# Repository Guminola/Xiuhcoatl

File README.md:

# Xiuhcoatl
Repositories of the Xiuhcoatl mission

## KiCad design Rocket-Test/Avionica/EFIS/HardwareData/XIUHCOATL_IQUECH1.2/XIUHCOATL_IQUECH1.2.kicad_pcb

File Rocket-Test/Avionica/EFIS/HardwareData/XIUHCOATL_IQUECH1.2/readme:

/*
  VERSION: XIUHCOATL_IQUECH 1.2

  PCB FILES
  KICAD:
  ".sch"=Esquema
  ".net"=Lista de Redes
  ".kicad_pcb"=PCB
  
  SPACE>COHETERIA>DIVEC>Jorge Guerrero
*/

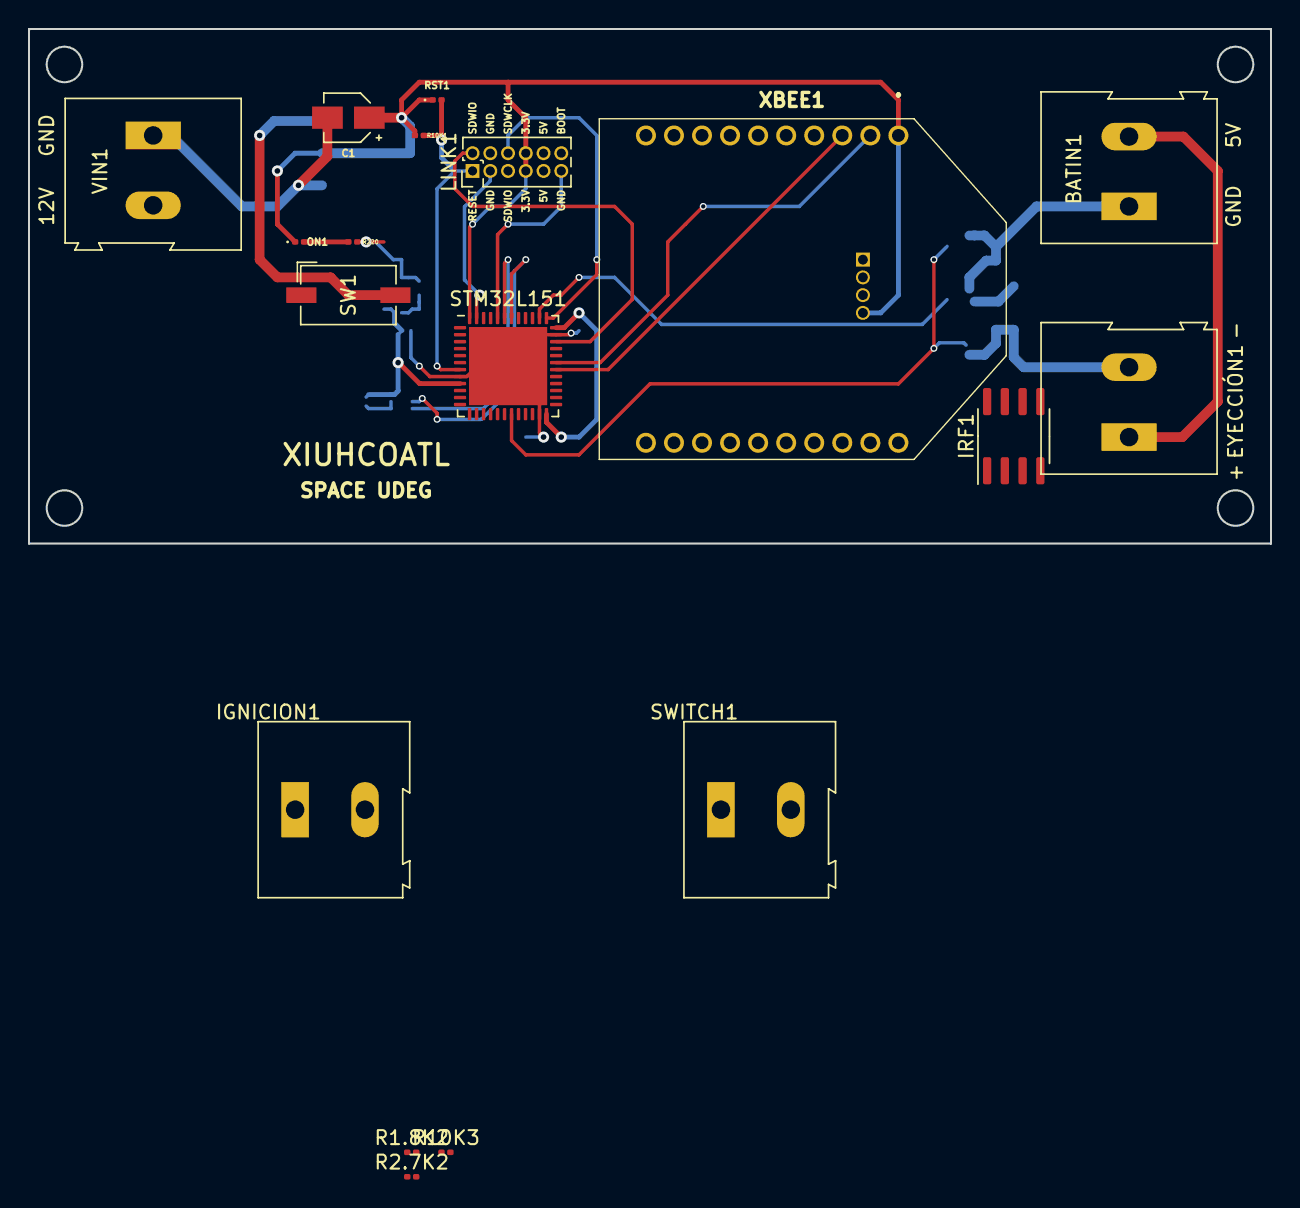
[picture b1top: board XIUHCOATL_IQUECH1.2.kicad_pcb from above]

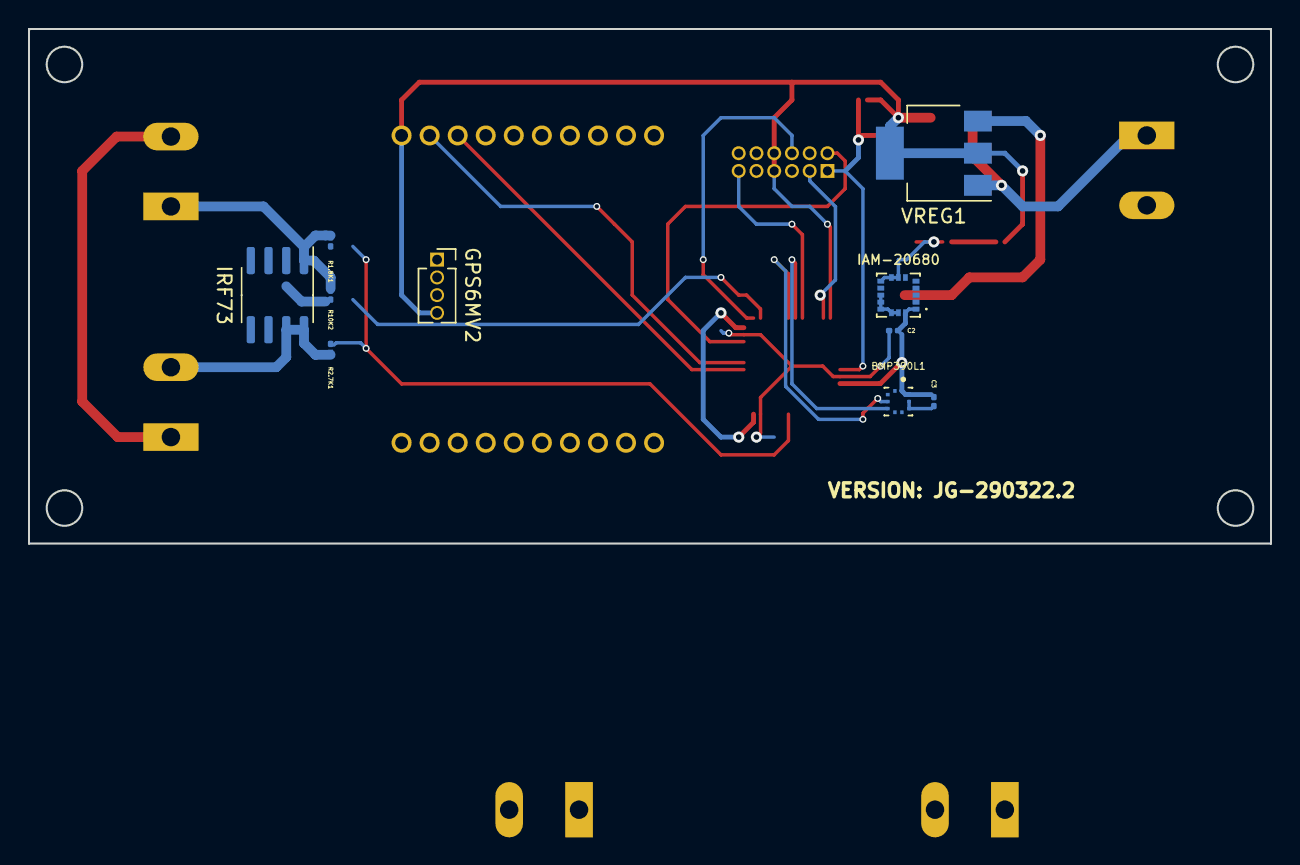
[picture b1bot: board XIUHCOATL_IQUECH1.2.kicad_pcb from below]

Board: 2 copper layers, 88.9 x 36.8 mm, 28 parts (10 on the bottom side), 22 nets.

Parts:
BATIN1: Screw_Terminal_01x02; TerminalBlock_Altech_AK300-2_P5.00mm
BMP390L1: BMP390L; XDCR_BMP390L
C1: 20; CP_Elec_3x5.3
C2, C3: CP; C_0201_0603Metric
EYECCIÓN1: Screw_Terminal_01x02; TerminalBlock_Altech_AK300-2_P5.00mm
GPS6MV2: Conn_01x04_Female; PinSocket_1x04_P1.27mm_Vertical
IAM-20680: IAM-20680; PQFN50P300X300X80-16N
IGNICION1: Screw_Terminal_01x02; TerminalBlock_Altech_AK300-2_P5.00mm
IRF1, IRF73: IRF7309IPBF; SOIC-8_3.9x4.9mm_P1.27mm
LINK1: Conn_01x12_Male; PinHeader_2x06_P1.27mm_Vertical
ON1: LED; LED_0201_0603Metric
R1.8K1, R1.8K2: 1.8K; R_0201_0603Metric
R2.7K1, R2.7K2: 2.7K; R_0201_0603Metric
R10K1, R10K2, R10K3: 10K; R_0201_0603Metric
R220: 220; R_0201_0603Metric
RST1: LED; LED_0201_0603Metric
STM32L151: STM32L151C6UxA; QFN-48-1EP_7x7mm_P0.5mm_EP5.6x5.6mm
SW1: SW_DIP_x01; SW_DIP_SPSTx01_Slide_6.7x4.1mm_W6.73mm_P2.54mm_LowProfile_J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
SWITCH1: Screw_Terminal_01x02; TerminalBlock_Altech_AK300-2_P5.00mm
VIN1: Screw_Terminal_01x02; TerminalBlock_Altech_AK300-2_P5.00mm
VREG1: AMS1117; SOT-223-3_TabPin2
XBEE1: XB24CZ7UITB003

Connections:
5V: BATIN1.2, EYECCIÓN1.1, IGNICION1.1
+12V: SW1.2, VREG1.3
BATGND: BATIN1.1, IRF1.1, IRF73.1, R1.8K1.1, R1.8K2.1, R10K2.1, R10K3.1
BMPSDI: BMP390L1.4, STM32L151.42
BMPSDO: BMP390L1.5, STM32L151.43
BOOT: LINK1.11, STM32L151.44
EYECCIÓN: IRF73.2, R10K2.2, STM32L151.33
GND: BMP390L1.3, BMP390L1.8, BMP390L1.9, C1.2, C2.2, C3.2, GPS6MV2.1, IAM-20680.7, IAM-20680.8, IAM-20680.9, IAM-20680.10, IAM-20680.11, IAM-20680.12, IAM-20680.13, IAM-20680.14, IAM-20680.15, LINK1.3, LINK1.4, LINK1.12, R220.2, STM32L151.8, STM32L151.23, STM32L151.35, STM32L151.47, STM32L151.49, VIN1.1, VREG1.1, XBEE1.10
IGNICION: IRF1.2, R10K3.2, STM32L151.38
LEDEYECCIÓN: R1.8K1.2, R2.7K1.1
LEDIGNICION: R1.8K2.2, R2.7K2.1, STM32L151.19
unnamed: EYECCIÓN1.2, IRF73.7, IRF73.8, R2.7K1.2
unnamed: IGNICION1.2, IRF1.7, IRF1.8, R2.7K2.2
unnamed: ON1.2, R220.1
RESET: LINK1.1, R10K1.1, RST1.2, STM32L151.7
RXBEE: STM32L151.30, XBEE1.3
SDWCLK: LINK1.6, STM32L151.37
SDWIO: LINK1.2, STM32L151.34
SW1: SWITCH1.2, VIN1.2
SW2: SW1.1, SWITCH1.1
TXBEE: STM32L151.31, XBEE1.2
VCC: BMP390L1.1, BMP390L1.10, C1.1, C2.1, C3.1, GPS6MV2.4, IAM-20680.1, IAM-20680.16, LINK1.7, LINK1.8, ON1.1, R10K1.2, RST1.1, STM32L151.9, STM32L151.24, STM32L151.36, STM32L151.48, VREG1.2, XBEE1.1

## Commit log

2024-04-17 imported files from old repository
